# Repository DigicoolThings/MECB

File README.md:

# Minimalist Europe Card Bus (MECB)

Europe Card Bus (ECB) is a Retro CPU Bus standard from the late 1970’s / early 1980’s.

The “Minimalist Europe Card Bus” (MECB), as I call it, is a Retro 8-bit CPU Bus based PCB design standard that I decided to define & document. The purpose of which is to provide a modular platform for me to re-experience the fun of experimenting with the different 8-bit CPU’s, and the various video and peripheral devices, that I grew up with in the late 1970’s and early 1980’s.

My goal is that of a robust and modular design platform which would allow me to create interchangeable boards, based on time proven reliable bus connectors and modern low-cost prototype PCB manufacturing.

i.e. A robust, flexible, and low cost way for me to re-create some of the early microprocessor circuits, that I’d originally built using Wire-Wrap methods back in the day.

As evident from the name, the Bus itself is based on a Minimalist implementation of the original Europe Card Bus (ECB) standard.

The included 'MECB_Template_16V8' and 'MECB_Template_22V10' folders contains KiCAD v9 Templates to enable fast-tracking new MECB board designs. 
This templates also include the standardised PLD (either 16V8 or 22V10), for Address Decoding, and is as illustrated in the Standardised Board Mechanical Specifications diagram below.

To utilise either Template, simply copy the entire Template folder and contents into your KiCAD v9 'KICAD_USER_TEMPLATE_DIR' path folder (as defined under: Preferences -> Configure Paths...).

More information on the Minimalist Europe Card Bus (MECB) can be found here: https://digicoolthings.com/minimalist-europe-card-bus-mecb

## MECB Board Mechanical (MECB_BoardMechanical.pdf)

## MECB Bus Pinout (MECB_Bus_Pinout.png)

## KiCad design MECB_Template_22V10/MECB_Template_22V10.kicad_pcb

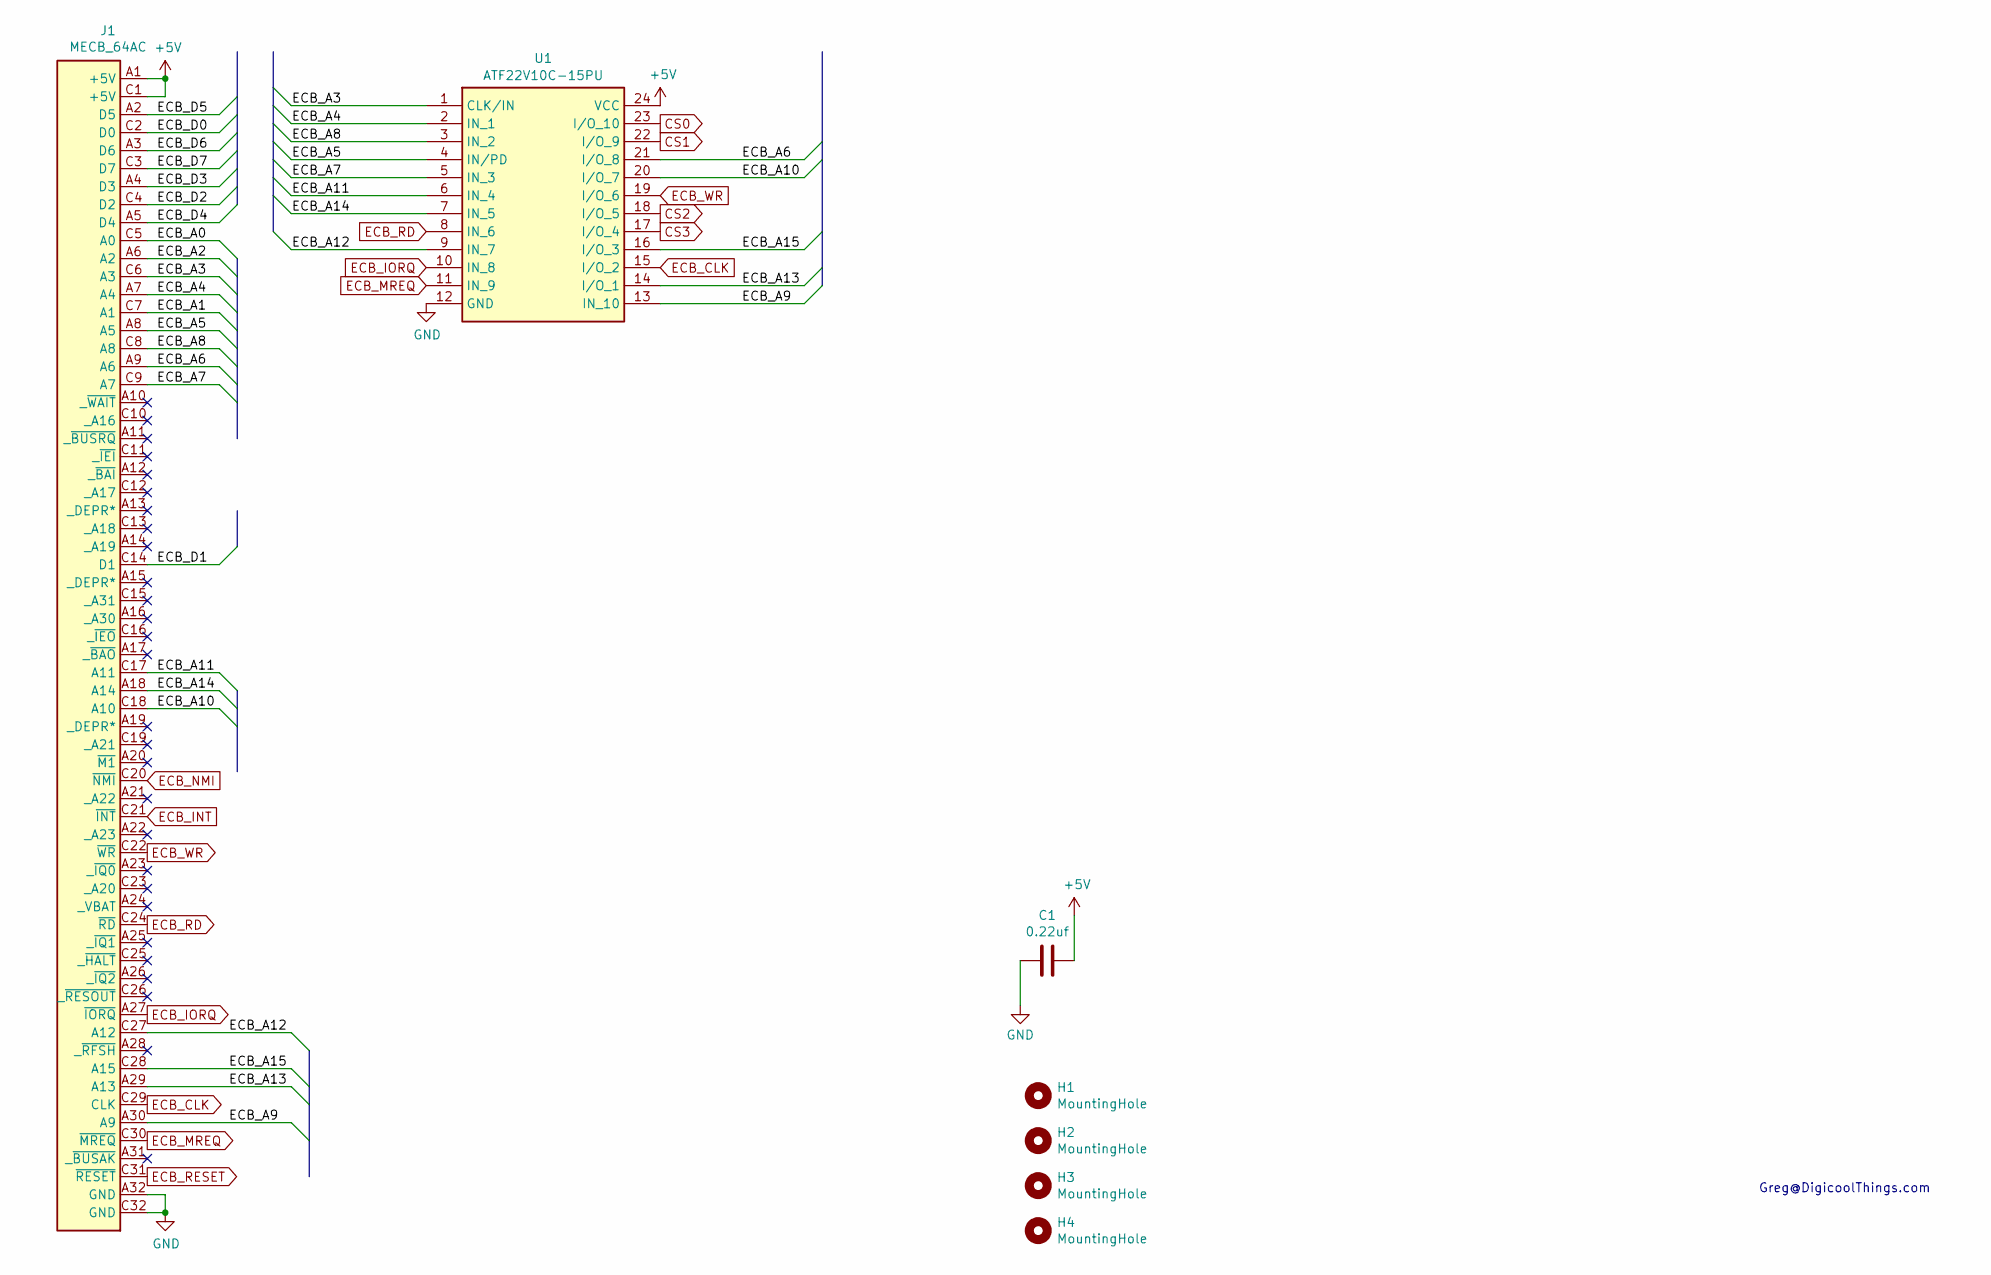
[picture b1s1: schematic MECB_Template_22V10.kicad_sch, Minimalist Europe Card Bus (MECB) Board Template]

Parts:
C1: 0.22uf; C_Disc_D5.0mm_W2.5mm_P5.00mm
H1, H2, H3, H4: MountingHole; MountingHole_3.2mm_M3
J1: MECB_64AC; DIN41612_C_2x32_C64AC_Male_Horizontal_THT
U1: ATF22V10C-15PU; DIP-24_W7.62mm_Socket_LongPads_ZIF_Friendly; Mouser Part Number 556-AF22V10C15PU

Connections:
+5V: C1.1, J1.A1 (+5V), J1.C1 (+5V), U1.24 (VCC)
/ECB_A0: J1.C5 (A0)
/ECB_A1: J1.C7 (A1)
/ECB_A2: J1.A6 (A2)
/ECB_A3: J1.C6 (A3), U1.1 (CLK/IN)
/ECB_A4: J1.A7 (A4), U1.2 (IN_1)
/ECB_A5: J1.A8 (A5), U1.4 (IN/PD)
/ECB_A6: J1.A9 (A6), U1.21 (I/O_8)
/ECB_A7: J1.C9 (A7), U1.5 (IN_3)
/ECB_A8: J1.C8 (A8), U1.3 (IN_2)
/ECB_A9: J1.A30 (A9), U1.13 (IN_10)
/ECB_A10: J1.C18 (A10), U1.20 (I/O_7)
/ECB_A11: J1.C17 (A11), U1.6 (IN_4)
/ECB_A12: J1.C27 (A12), U1.9 (IN_7)
/ECB_A13: J1.A29 (A13), U1.14 (I/O_1)
/ECB_A14: J1.A18 (A14), U1.7 (IN_5)
/ECB_A15: J1.C28 (A15), U1.16 (I/O_3)
/ECB_D0: J1.C2 (D0)
/ECB_D1: J1.C14 (D1)
/ECB_D2: J1.C4 (D2)
/ECB_D3: J1.A4 (D3)
/ECB_D4: J1.A5 (D4)
/ECB_D5: J1.A2 (D5)
/ECB_D6: J1.A3 (D6)
/ECB_D7: J1.C3 (D7)
CS0: U1.23 (I/O_10)
CS1: U1.22 (I/O_9)
CS2: U1.18 (I/O_5)
CS3: U1.17 (I/O_4)
ECB_CLK: J1.C29 (CLK), U1.15 (I/O_2)
ECB_INT: J1.C21 (~INT)
ECB_IORQ: J1.A27 (~IORQ), U1.10 (IN_8)
ECB_MREQ: J1.C30 (~MREQ), U1.11 (IN_9)
ECB_NMI: J1.C20 (~NMI)
ECB_RD: J1.C24 (~RD), U1.8 (IN_6)
ECB_RESET: J1.C31 (~RESET)
ECB_WR: J1.C22 (~WR), U1.19 (I/O_6)
GND: C1.2, J1.A32 (GND), J1.C32 (GND), U1.12 (GND)

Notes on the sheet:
Greg@DigicoolThings.com

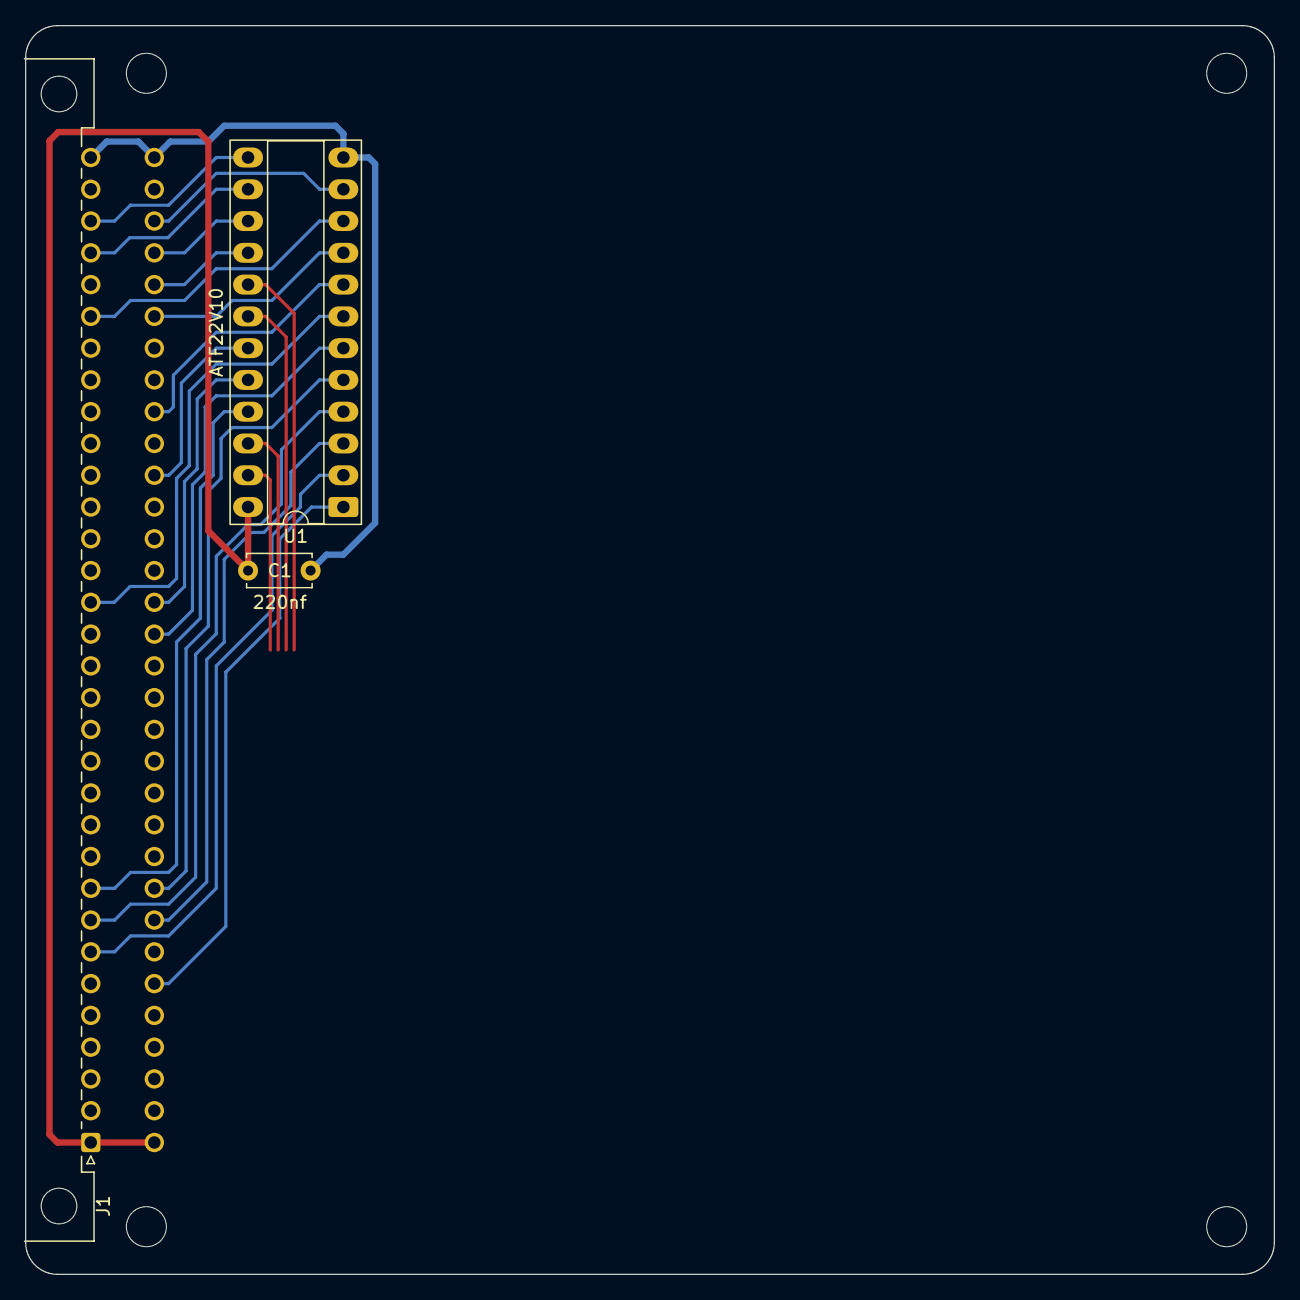
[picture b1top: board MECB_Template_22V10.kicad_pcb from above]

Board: 2 copper layers, 99.8 x 99.8 mm, 7 parts (0 on the bottom side), 20 nets.

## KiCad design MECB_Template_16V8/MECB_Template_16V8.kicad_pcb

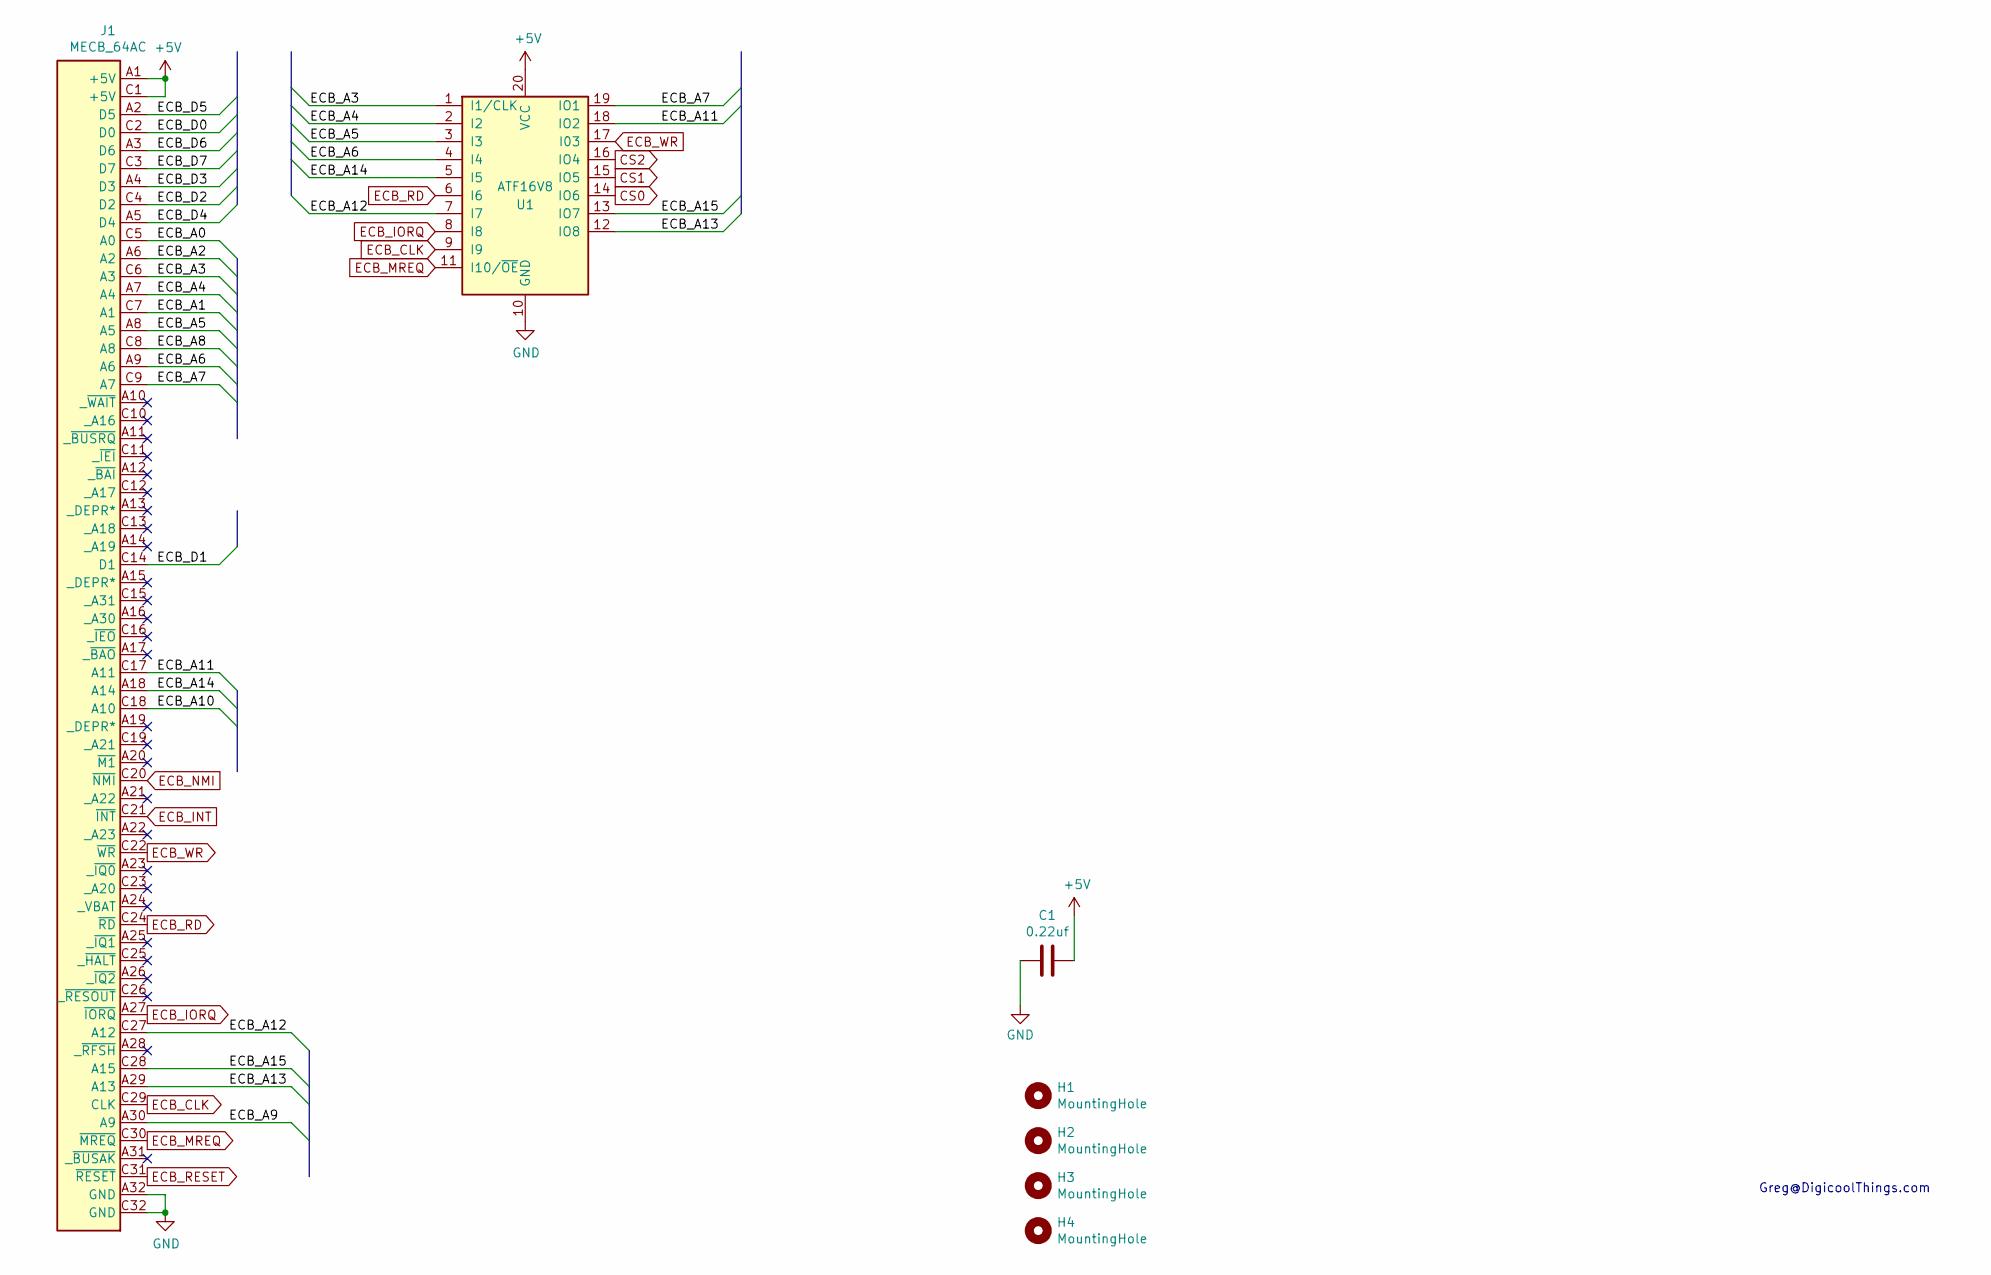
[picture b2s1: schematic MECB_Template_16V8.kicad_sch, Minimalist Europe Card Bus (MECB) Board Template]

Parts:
C1: 0.22uf; C_Disc_D5.0mm_W2.5mm_P5.00mm
H1, H2, H3, H4: MountingHole; MountingHole_3.2mm_M3
J1: MECB_64AC; DIN41612_C_2x32_C64AC_Male_Horizontal_THT
U1: ATF16V8; DIP-20_W7.62mm_Socket_LongPads_ZIF_friendly

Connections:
+5V: C1.1, J1.A1 (+5V), J1.C1 (+5V), U1.20 (VCC)
/ECB_A0: J1.C5 (A0)
/ECB_A1: J1.C7 (A1)
/ECB_A2: J1.A6 (A2)
/ECB_A3: J1.C6 (A3), U1.1 (I1/CLK)
/ECB_A4: J1.A7 (A4), U1.2 (I2)
/ECB_A5: J1.A8 (A5), U1.3 (I3)
/ECB_A6: J1.A9 (A6), U1.4 (I4)
/ECB_A7: J1.C9 (A7), U1.19 (IO1)
/ECB_A8: J1.C8 (A8)
/ECB_A9: J1.A30 (A9)
/ECB_A10: J1.C18 (A10)
/ECB_A11: J1.C17 (A11), U1.18 (IO2)
/ECB_A12: J1.C27 (A12), U1.7 (I7)
/ECB_A13: J1.A29 (A13), U1.12 (IO8)
/ECB_A14: J1.A18 (A14), U1.5 (I5)
/ECB_A15: J1.C28 (A15), U1.13 (IO7)
/ECB_D0: J1.C2 (D0)
/ECB_D1: J1.C14 (D1)
/ECB_D2: J1.C4 (D2)
/ECB_D3: J1.A4 (D3)
/ECB_D4: J1.A5 (D4)
/ECB_D5: J1.A2 (D5)
/ECB_D6: J1.A3 (D6)
/ECB_D7: J1.C3 (D7)
CS0: U1.14 (IO6)
CS1: U1.15 (IO5)
CS2: U1.16 (IO4)
ECB_CLK: J1.C29 (CLK), U1.9 (I9)
ECB_INT: J1.C21 (~INT)
ECB_IORQ: J1.A27 (~IORQ), U1.8 (I8)
ECB_MREQ: J1.C30 (~MREQ), U1.11 (I10/~OE)
ECB_NMI: J1.C20 (~NMI)
ECB_RD: J1.C24 (~RD), U1.6 (I6)
ECB_RESET: J1.C31 (~RESET)
ECB_WR: J1.C22 (~WR), U1.17 (I03)
GND: C1.2, J1.A32 (GND), J1.C32 (GND), U1.10 (GND)

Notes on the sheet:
Greg@DigicoolThings.com

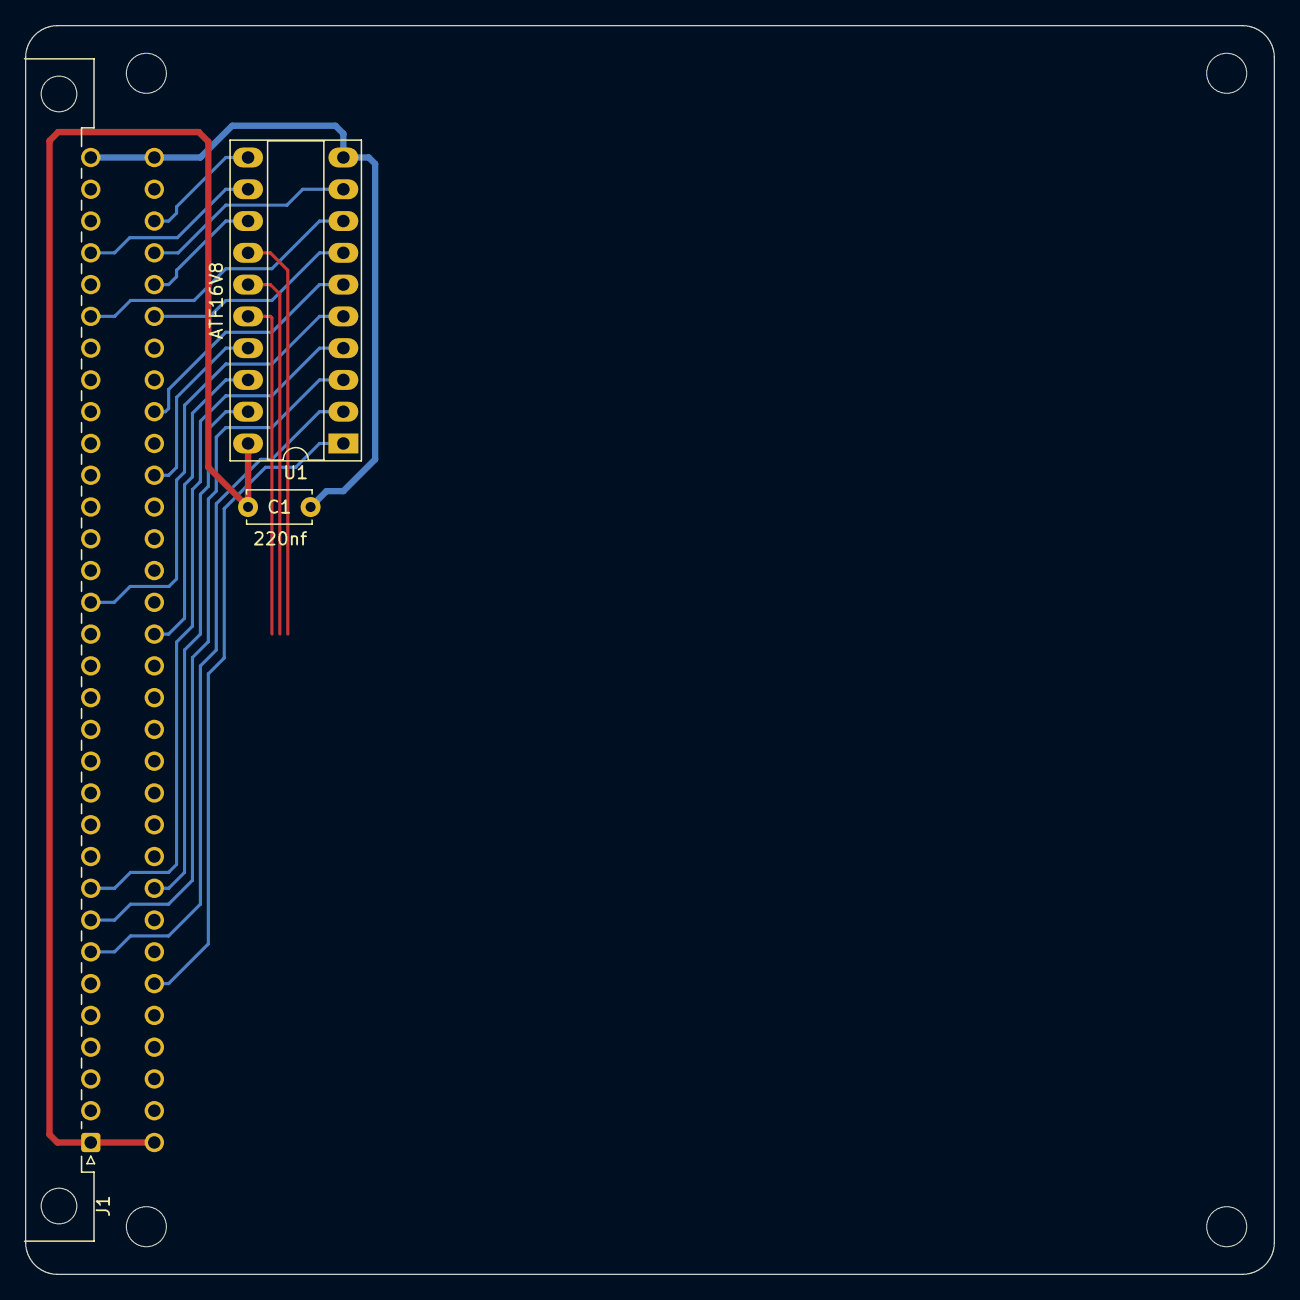
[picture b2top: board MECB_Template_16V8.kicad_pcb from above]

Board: 2 copper layers, 99.8 x 99.8 mm, 7 parts (0 on the bottom side), 17 nets.

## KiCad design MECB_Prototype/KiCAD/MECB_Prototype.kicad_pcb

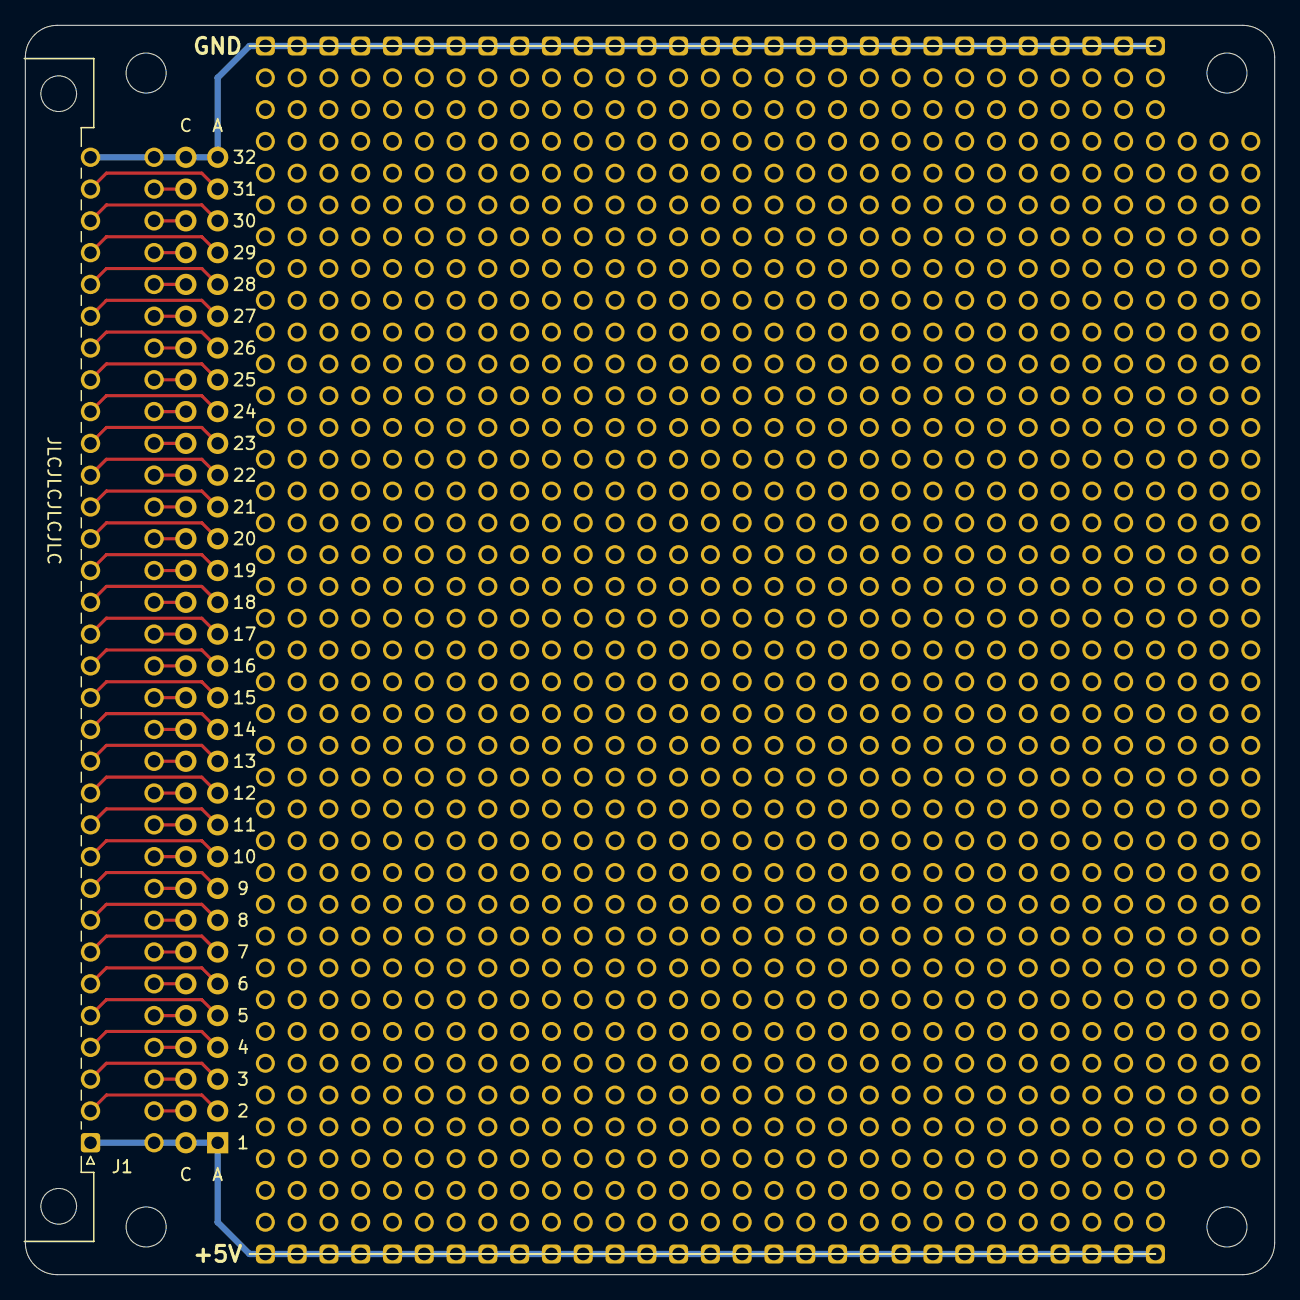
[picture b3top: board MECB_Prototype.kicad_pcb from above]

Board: 2 copper layers, 99.8 x 99.8 mm, 8 parts (0 on the bottom side), 62 nets.

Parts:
H1, H2, H3, H4: MountingHole; MountingHole_3.2mm_M3
J1: MECB_64AC; DIN41612_C_2x32_C64AC_Male_Horizontal_THT
J2: Conn_01x32_Male; PinHeader_2x32_P2.54mm_Vertical_A1-B32
P1: CONN_2X2; Pad_Array_2.54mm_MECB_Proto_Full
P2: CONN_2X2; Pad_Array_2.54mm_MECB_Proto_Power

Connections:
+5V: J1.A1, J1.C1, J2.A1, J2.B1, P2.1, P2.3
ECB_A0: J1.C5, J2.B5
ECB_A1: J1.C7, J2.B7
ECB_A2: J1.A6, J2.A6
ECB_A3: J1.C6, J2.B6
ECB_A4: J1.A7, J2.A7
ECB_A5: J1.A8, J2.A8
ECB_A6: J1.A9, J2.A9
ECB_A7: J1.C9, J2.B9
ECB_A8: J1.C8, J2.B8
ECB_A9: J1.A30, J2.A30
ECB_A10: J1.C18, J2.B18
ECB_A11: J1.C17, J2.B17
ECB_A12: J1.C27, J2.B27
ECB_A13: J1.A29, J2.A29
ECB_A14: J1.A18, J2.A18
ECB_A15: J1.C28, J2.B28
ECB_A16: J1.C10, J2.B10
ECB_A17: J1.C12, J2.B12
ECB_A18: J1.C13, J2.B13
ECB_A19: J1.A14, J2.A14
ECB_A20: J1.C23, J2.B23
ECB_A21: J1.C19, J2.B19
ECB_A22: J1.A21, J2.A21
ECB_A23: J1.A22, J2.A22
ECB_A30: J1.A16, J2.A16
ECB_A31: J1.C15, J2.B15
ECB_BAI: J1.A12, J2.A12
ECB_BAO: J1.A17, J2.A17
ECB_BUSAK: J1.A31, J2.A31
ECB_BUSRQ: J1.A11, J2.A11
ECB_CLK: J1.C29, J2.B29
ECB_D0: J1.C2, J2.B2
ECB_D1: J1.C14, J2.B14
ECB_D2: J1.C4, J2.B4
ECB_D3: J1.A4, J2.A4
ECB_D4: J1.A5, J2.A5
ECB_D5: J1.A2, J2.A2
ECB_D6: J1.A3, J2.A3
ECB_D7: J1.C3, J2.B3
ECB_DEPR1: J1.A19, J2.A19
ECB_DEPR2: J1.A15, J2.A15
ECB_DEPR3: J1.A13, J2.A13
ECB_HALT: J1.C25, J2.B25
ECB_IEI: J1.C11, J2.B11
ECB_IEO: J1.C16, J2.B16
ECB_INT: J1.C21, J2.B21
ECB_IORQ: J1.A27, J2.A27
ECB_IQ0: J1.A23, J2.A23
ECB_IQ1: J1.A25, J2.A25
ECB_IQ2: J1.A26, J2.A26
ECB_M1: J1.A20, J2.A20
ECB_MREQ: J1.C30, J2.B30
ECB_NMI: J1.C20, J2.B20
ECB_RD: J1.C24, J2.B24
ECB_RESET: J1.C31, J2.B31
ECB_RESOUT: J1.C26, J2.B26
ECB_RFSH: J1.A28, J2.A28
ECB_VBAT: J1.A24, J2.A24
ECB_WAIT: J1.A10, J2.A10
ECB_WR: J1.C22, J2.B22
GND: J1.A32, J1.C32, J2.A32, J2.B32, P2.1, P2.3

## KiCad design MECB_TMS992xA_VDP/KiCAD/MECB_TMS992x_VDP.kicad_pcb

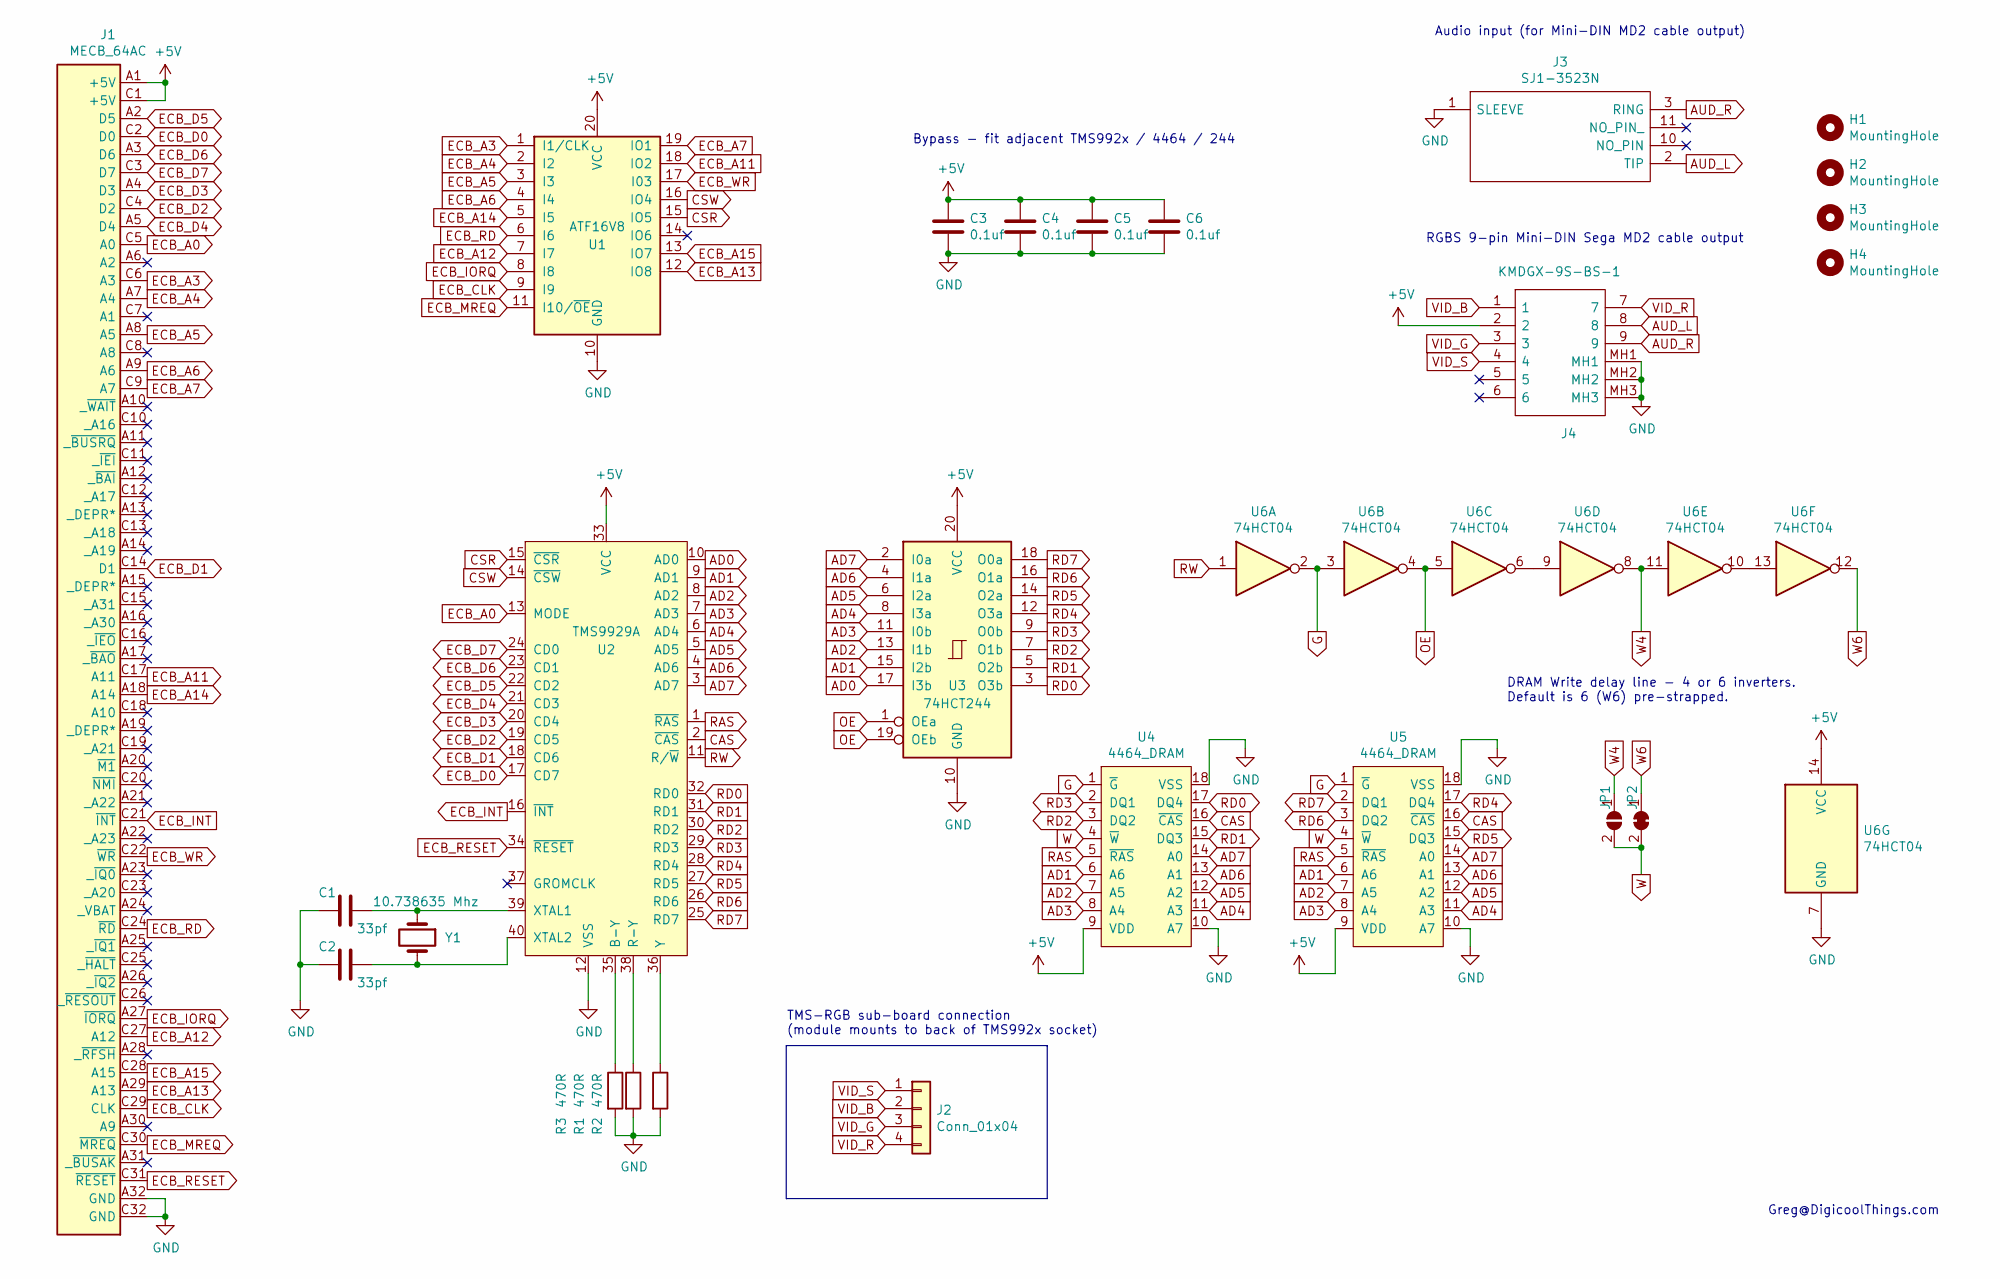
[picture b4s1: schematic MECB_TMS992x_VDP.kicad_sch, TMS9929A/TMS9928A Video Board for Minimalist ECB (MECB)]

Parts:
C1, C2: 33pf; C_Disc_D4.3mm_W1.9mm_P5.00mm
C3, C4, C5, C6: 0.1uf; C_Disc_D5.0mm_W2.5mm_P5.00mm
H1, H2, H3, H4: MountingHole; MountingHole_3.2mm_M3
J1: MECB_64AC; DIN41612_C_2x32_C64AC_Male_Horizontal_THT
J2: Conn_01x04; PinHeader_1x04_P2.54mm_Horizontal
J3: SJ1-3523N; SJ13523N; Mouser Part Number 490-SJ1-3523N
J4: KMDGX-9S-BS-1; KMDGX9SBS1; Manufacturer_Part_Number KMDGX-9S-BS-1; Mouser Part Number 806-KMDGX-9S-BS-1
JP1: SolderJumper_2_Open; SolderJumper-2_P1.3mm_Open_RoundedPad1.0x1.5mm
JP2: SolderJumper_2_Bridged; SolderJumper-2_P1.3mm_Bridged_RoundedPad1.0x1.5mm
R1, R2, R3: 470R; R_Axial_DIN0207_L6.3mm_D2.5mm_P7.62mm_Horizontal
U1: ATF16V8; DIP-20_W7.62mm_Socket_LongPads
U2: TMS9929A; DIP-40_W15.24mm_Socket_LongPads
U3: 74HCT244; DIP-20_W7.62mm_Socket_LongPads
U4, U5: 4464_DRAM; DIP-18_W7.62mm_Socket_LongPads
U6: 74HCT04; DIP-14_W7.62mm_Socket_LongPads
Y1: 10.738635 Mhz; Crystal_HC49-U_Vertical

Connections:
+5V: C3.1, C4.1, C5.1, C6.1, J1.A1 (+5V), J1.C1 (+5V), J4.2, U1.20 (VCC), U2.33 (VCC), U3.20 (VCC), U4.9 (VDD), U5.9 (VDD), U6.14 (VCC)
AD0: U2.10 (AD0), U3.17 (I3b)
AD1: U2.9 (AD1), U3.15 (I2b), U4.6 (A6), U5.6 (A6)
AD2: U2.8 (AD2), U3.13 (I1b), U4.7 (A5), U5.7 (A5)
AD3: U2.7 (AD3), U3.11 (I0b), U4.8 (A4), U5.8 (A4)
AD4: U2.6 (AD4), U3.8 (I3a), U4.11 (A3), U5.11 (A3)
AD5: U2.5 (AD5), U3.6 (I2a), U4.12 (A2), U5.12 (A2)
AD6: U2.4 (AD6), U3.4 (I1a), U4.13 (A1), U5.13 (A1)
AD7: U2.3 (AD7), U3.2 (I0a), U4.14 (A0), U5.14 (A0)
AUD_L: J3.2 (TIP), J4.8
AUD_R: J3.3 (RING), J4.9
CAS: U2.2 (~CAS), U4.16 (~CAS), U5.16 (~CAS)
CSR: U1.15 (IO5), U2.15 (~CSR)
CSW: U1.16 (IO4), U2.14 (~CSW)
ECB_A0: J1.C5 (A0), U2.13 (MODE)
ECB_A3: J1.C6 (A3), U1.1 (I1/CLK)
ECB_A4: J1.A7 (A4), U1.2 (I2)
ECB_A5: J1.A8 (A5), U1.3 (I3)
ECB_A6: J1.A9 (A6), U1.4 (I4)
ECB_A7: J1.C9 (A7), U1.19 (IO1)
ECB_A11: J1.C17 (A11), U1.18 (IO2)
ECB_A12: J1.C27 (A12), U1.7 (I7)
ECB_A13: J1.A29 (A13), U1.12 (IO8)
ECB_A14: J1.A18 (A14), U1.5 (I5)
ECB_A15: J1.C28 (A15), U1.13 (IO7)
ECB_CLK: J1.C29 (CLK), U1.9 (I9)
ECB_D0: J1.C2 (D0), U2.17 (CD7)
ECB_D1: J1.C14 (D1), U2.18 (CD6)
ECB_D2: J1.C4 (D2), U2.19 (CD5)
ECB_D3: J1.A4 (D3), U2.20 (CD4)
ECB_D4: J1.A5 (D4), U2.21 (CD3)
ECB_D5: J1.A2 (D5), U2.22 (CD2)
ECB_D6: J1.A3 (D6), U2.23 (CD1)
ECB_D7: J1.C3 (D7), U2.24 (CD0)
ECB_INT: J1.C21 (~INT), U2.16 (~INT)
ECB_IORQ: J1.A27 (~IORQ), U1.8 (I8)
ECB_MREQ: J1.C30 (~MREQ), U1.11 (I10/~OE)
ECB_RD: J1.C24 (~RD), U1.6 (I6)
ECB_RESET: J1.C31 (~RESET), U2.34 (~RESET)
ECB_WR: J1.C22 (~WR), U1.17 (I03)
G: U4.1 (~G), U5.1 (~G), U6.2, U6.3
GND: C1.2, C2.2, C3.2, C4.2, C5.2, C6.2, J1.A32 (GND), J1.C32 (GND), J3.1 (SLEEVE), J4.MH1, J4.MH2, J4.MH3, R1.2, R2.2, R3.2, U1.10 (GND), U2.12 (VSS), U3.10 (GND), U4.10 (A7), U4.18 (VSS), U5.10 (A7), U5.18 (VSS), U6.7 (GND)
unnamed: R3.1, U2.35 (B-Y)
unnamed: R1.1, U2.38 (R-Y)
unnamed: C1.1, U2.39 (XTAL1), Y1.1
unnamed: C2.1, U2.40 (XTAL2), Y1.2
unnamed: R2.1, U2.36 (Y)
unnamed: U6.6, U6.9
unnamed: U6.10, U6.13
OE: U3.1 (OEa), U3.19 (OEb), U6.4, U6.5
RAS: U2.1 (~RAS), U4.5 (~RAS), U5.5 (~RAS)
RD0: U2.32 (RD0), U3.3 (O3b), U4.17 (DQ4)
RD1: U2.31 (RD1), U3.5 (O2b), U4.15 (DQ3)
RD2: U2.30 (RD2), U3.7 (O1b), U4.3 (DQ2)
RD3: U2.29 (RD3), U3.9 (O0b), U4.2 (DQ1)
RD4: U2.28 (RD4), U3.12 (O3a), U5.17 (DQ4)
RD5: U2.27 (RD5), U3.14 (O2a), U5.15 (DQ3)
RD6: U2.26 (RD6), U3.16 (O1a), U5.3 (DQ2)
RD7: U2.25 (RD7), U3.18 (O0a), U5.2 (DQ1)
RW: U2.11 (R/~W), U6.1
VID_B: J2.2, J4.1
VID_G: J2.3, J4.3
VID_R: J2.4, J4.7
VID_S: J2.1, J4.4
W: JP1.2 (B), JP2.2 (B), U4.4 (~W), U5.4 (~W)
W4: JP1.1 (A), U6.8, U6.11
W6: JP2.1 (A), U6.12

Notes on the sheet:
TMS-RGB sub-board connection (module mounts to back of TMS992x socket)
RGBS 9-pin Mini-DIN Sega MD2 cable output
DRAM Write delay line - 4 or 6 inverters. Default is 6 (W6) pre-strapped.
Bypass - fit adjacent TMS992x / 4464 / 244
Greg@DigicoolThings.com
Audio input (for Mini-DIN MD2 cable output)

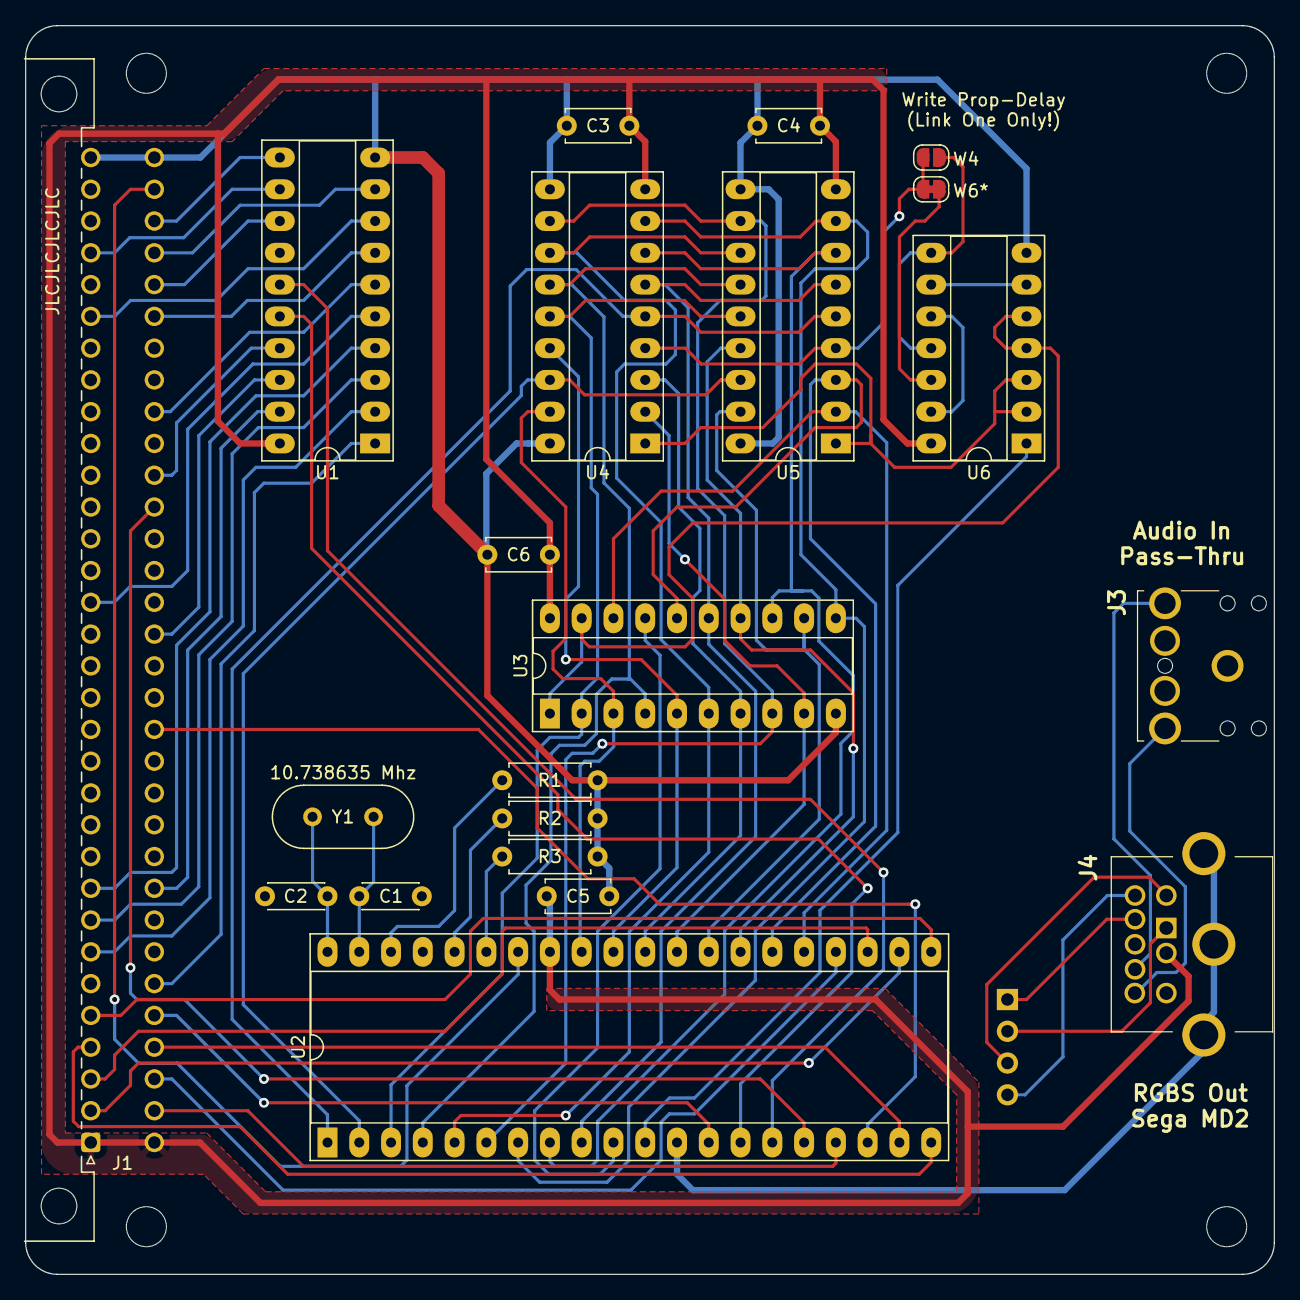
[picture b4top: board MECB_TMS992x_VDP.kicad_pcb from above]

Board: 2 copper layers, 99.8 x 99.8 mm, 26 parts (1 on the bottom side), 67 nets.
